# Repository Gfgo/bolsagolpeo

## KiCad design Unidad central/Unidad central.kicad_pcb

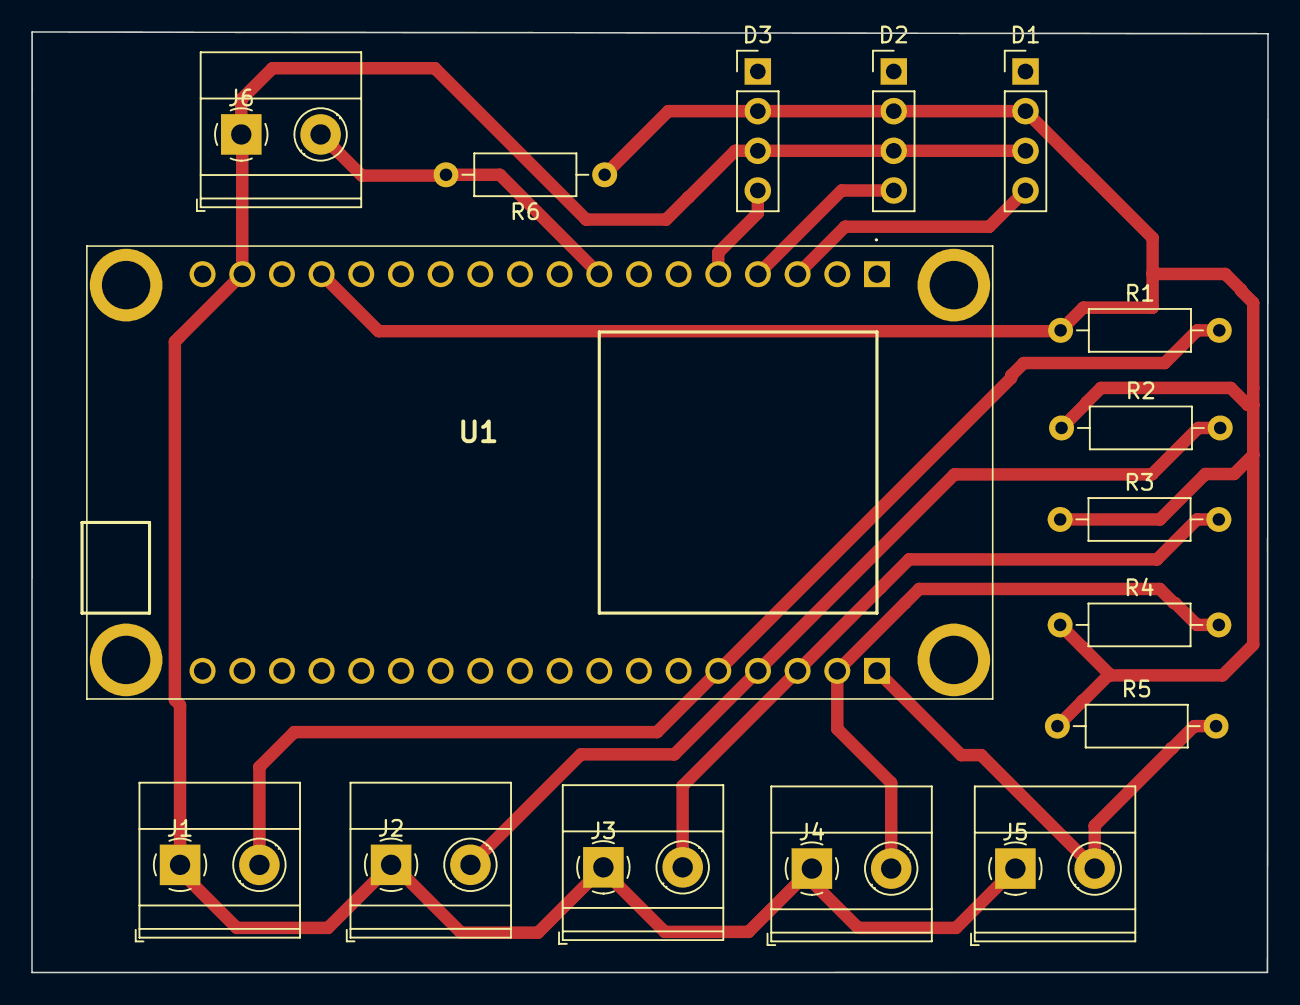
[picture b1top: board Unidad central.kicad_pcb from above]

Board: 2 copper layers, 79.1 x 60.2 mm, 16 parts (0 on the bottom side), 11 nets.

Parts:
D1, D2, D3: NeoPixel_THT; PinHeader_1x04_P2.54mm_Vertical
J1, J2, J3, J4, J5, J6: Conn_01x02; TerminalBlock_Phoenix_MKDS-1,5-2-5.08_1x02_P5.08mm_Horizont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
R1, R2, R3, R4, R5, R6: R; R_Axial_DIN0207_L6.3mm_D2.5mm_P10.16mm_Horizontal
U1: DFR0478; Esp32DFR0478

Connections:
unnamed: D1.2, D2.2, D3.2, R1.1, R2.1, R3.1, R4.1, R5.1, R6.1, U1.15
unnamed: D1.3, D2.3, D3.3, J1.1, J2.1, J3.1, J4.1, J5.1, J6.1, U1.17
unnamed: D1.4, U1.3
unnamed: D2.4, U1.4
unnamed: D3.4, U1.5
unnamed: J1.2, R1.2, U1.23
unnamed: J2.2, R2.2, U1.22
unnamed: J3.2, R3.2, U1.21
unnamed: J4.2, R4.2, U1.20
unnamed: J5.2, R5.2, U1.19
unnamed: J6.2, R6.2, U1.8

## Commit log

2021-10-09 Create bolsagolpeo.ino
    Lectura de potencia de golpe.
2021-10-11 Update bolsagolpeo.ino
    Leo golpe lo imprimo en pantalla y doy indicación visual de potencia.
2021-10-12 Update bolsagolpeo.ino
    Lectura de golpe con medidor de fuerza visual
2021-10-13 Update bolsagolpeo.ino
    Programacion mejorada
2021-10-19 Update bolsagolpeo.ino
    Medida en Kg+Barra de poder
2021-10-20 Update bolsagolpeo.ino
    Programación 20/10
2021-10-27 Update bolsagolpeo.ino
    Lectura 2 sensores e impresion de valores.
2022-03-22 Revert "Update bolsagolpeo.ino"
    This reverts commit b2e1f5cbca1a3fcc65236e804a6ba07a1650a82e.
2022-05-19 Update bolsagolpeo.ino
    19/05 Cambio a esp con 3 lecturas simultaneas al tiempo
2022-05-24 Sensor y barra ok
    Sensor y barras funcionando, impresion de valor sin espera
2022-06-30 Circuito con borneras y ultima versión de software funcionando.
    Circuito con borneras y ultima versión de software funcionando.
2023-06-20 acceleración
2023-06-21 21/06 calibracion
2023-06-22 22/06
    gz no afcta z1 o z2
2023-06-23 Update bolsagolpeo.ino
    La calibracion en caliente no funciona
2023-06-24 Fuerza total implementada
2023-06-26 calculo de fuerza con masa dada.
